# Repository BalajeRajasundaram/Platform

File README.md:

# Platform
SAMD20 Base board

Using https://github.com/SchrodingersGat/KiBoM for BOM generation.

Using https://github.com/ian-ross/kicad-plugins for auto placement of components initially.

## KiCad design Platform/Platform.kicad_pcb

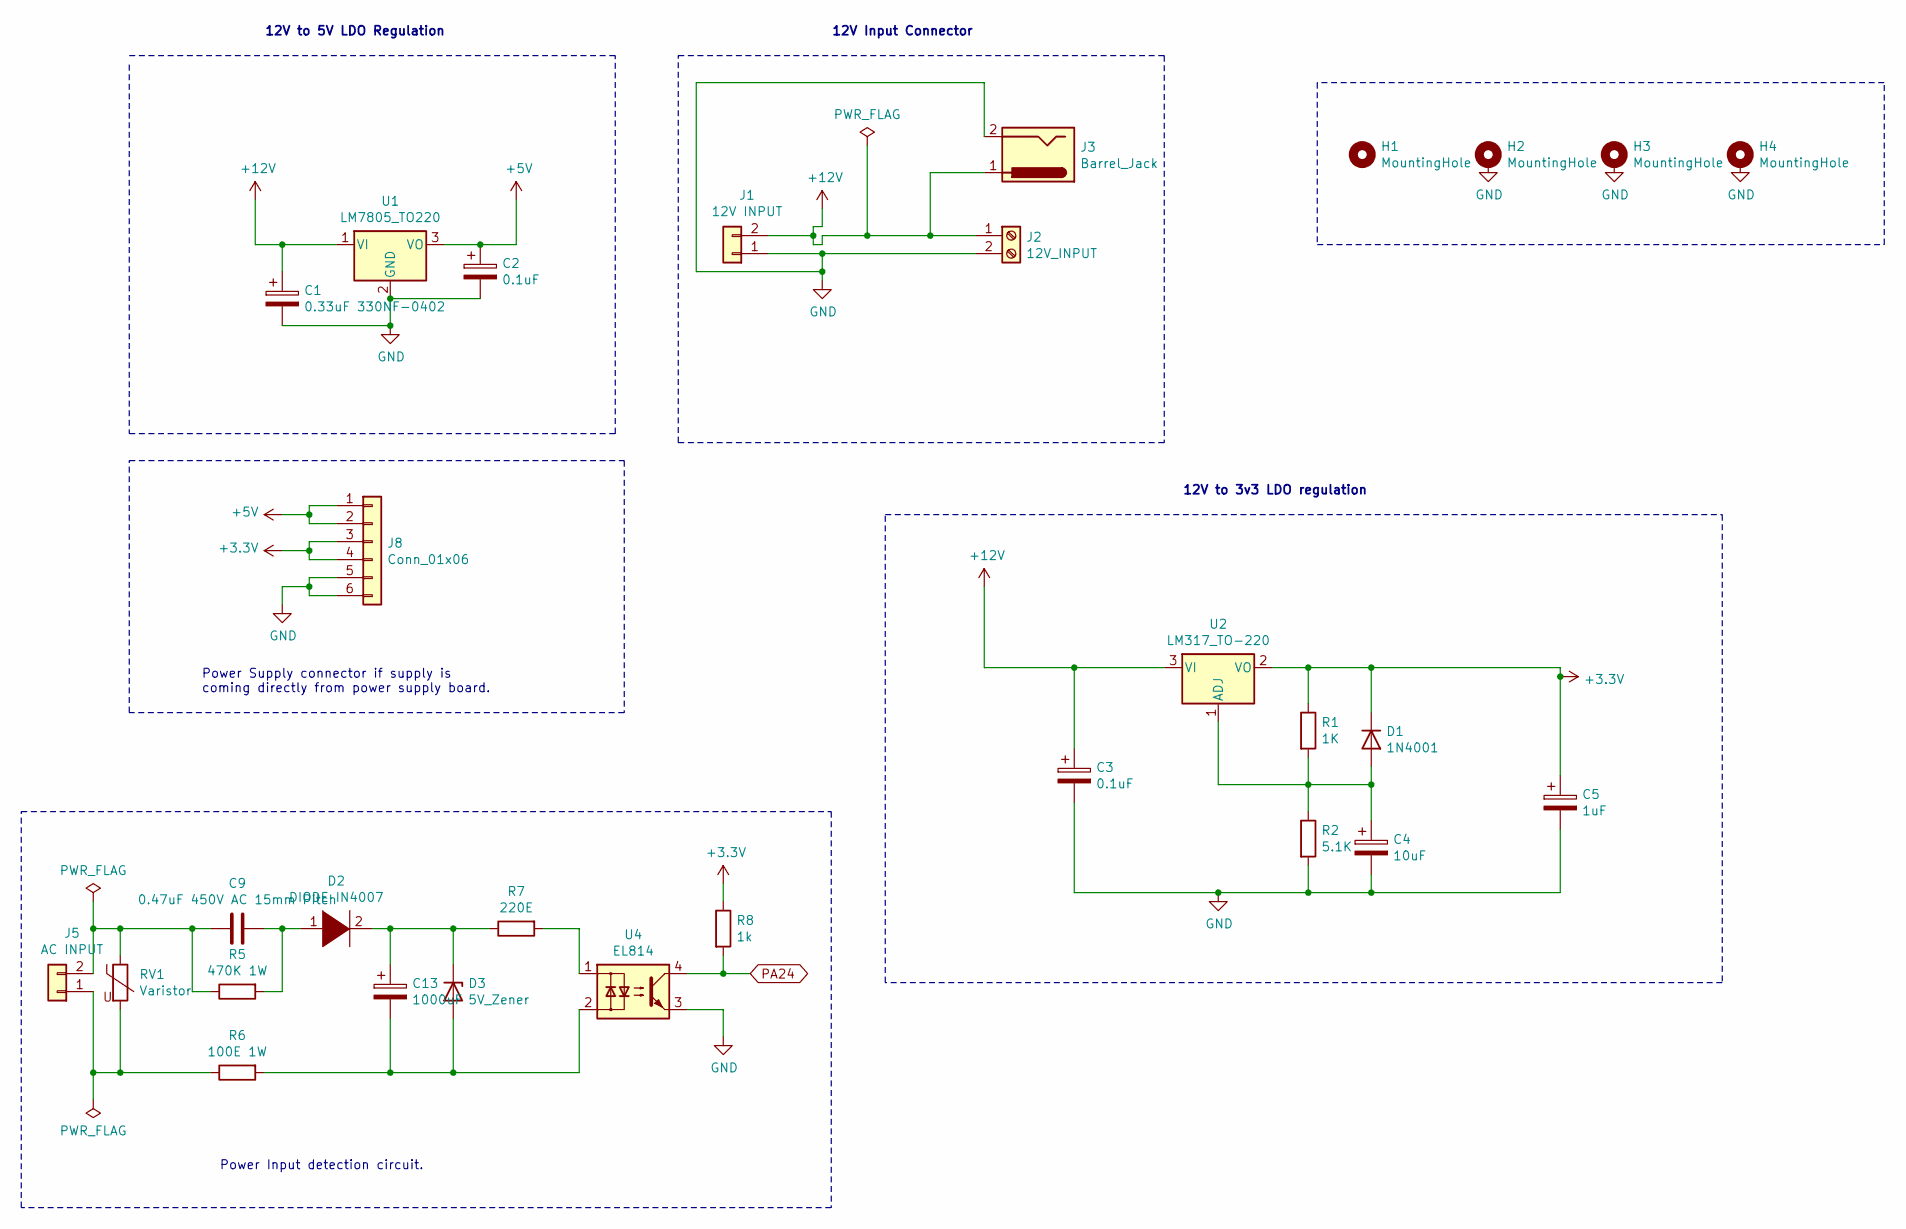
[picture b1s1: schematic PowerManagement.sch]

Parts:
C1: 0.33uF 330NF-0402; C_0402_1005Metric
C2, C3: 0.1uF; C_0402_1005Metric
C4: 10uF; CP_Radial_Tantal_D5.0mm_P5.00mm
C5: 1uF; CP_Radial_Tantal_D5.0mm_P5.00mm
C9: 0.47uF 450V AC 15mm Pitch; C_Rect_L7.2mm_W5.5mm_P5.00mm_FKS2_FKP2_MKS2_MKP2
C13: 1000uF; CP_Radial_D10.0mm_P2.50mm
D1: 1N4001; D_DO-41_SOD81_P10.16mm_Horizontal
D2: DIODE IN4007; D_DO-41_SOD81_P10.16mm_Horizontal
D3: 5V_Zener; D_DO-35_SOD27_P7.62mm_Horizontal
H1, H2, H3, H4: MountingHole; MountingHole_3.2mm_M3_DIN965_Pad
J1: 12V INPUT; TerminalBlock_Phoenix_MKDS-1,5-2_1x02_P5.00mm_Horizontal
J2: 12V_INPUT; PinHeader_1x02_P2.54mm_Vertical
J3: Barrel_Jack; BarrelJack_Horizontal
J5: AC INPUT; TerminalBlock_Phoenix_MKDS-1,5-2_1x02_P5.00mm_Horizontal
J8: Conn_01x06; Molex_KK-254_AE-6410-06A_1x06_P2.54mm_Vertical
R1: 1K; R_0603_1608Metric
R2: 5.1K; R_0603_1608Metric
R5: 470K 1W; R_Axial_DIN0411_L9.9mm_D3.6mm_P12.70mm_Horizontal
R6: 100E 1W; R_Axial_DIN0411_L9.9mm_D3.6mm_P12.70mm_Horizontal
R7: 220E; R_0603_1608Metric
R8: 1k; R_0603_1608Metric
RV1: Varistor; RV_Disc_D7mm_W3.4mm_P5mm
U1: LM7805_TO220; TO-220-3_Vertical
U2: LM317_TO-220; TO-220-3_Vertical
U4: EL814; Luna_NSL-32

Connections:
+3V3: C5.1, D1.1 (K), J8.3, J8.4, R1.1, R8.1, U2.2 (VO); also elsewhere on the board
+5V: C2.1, J8.1, J8.2, U1.3 (VO); also elsewhere on the board
+12V: C1.1, C3.1, J1.2, J2.1, J3.1, U1.1 (VI), U2.3 (VI)
GND: C1.2, C2.2, C3.2, C4.2, C5.2, J1.1, J2.2, J3.2, J8.5, J8.6, R2.2, U1.2 (GND), U4.3; also elsewhere on the board
unnamed: C4.1, D1.2 (A), R1.2, R2.1, U2.1 (ADJ)
unnamed: C9.1, J5.2, R5.1, RV1.1
unnamed: C9.2, D2.1 (K), R5.2
unnamed: C13.1, D2.2 (A), D3.1 (K), R7.1
unnamed: C13.2, D3.2 (A), R6.2, U4.2
unnamed: J5.1, R6.1, RV1.2
unnamed: R7.2, U4.1
PA24: R8.2, U4.4; also elsewhere on the board

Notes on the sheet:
12V Input Connector
12V to 5V LDO Regulation
12V to 3v3 LDO regulation
Power Supply connector if supply is coming directly from power supply board.
Power Input detection circuit.

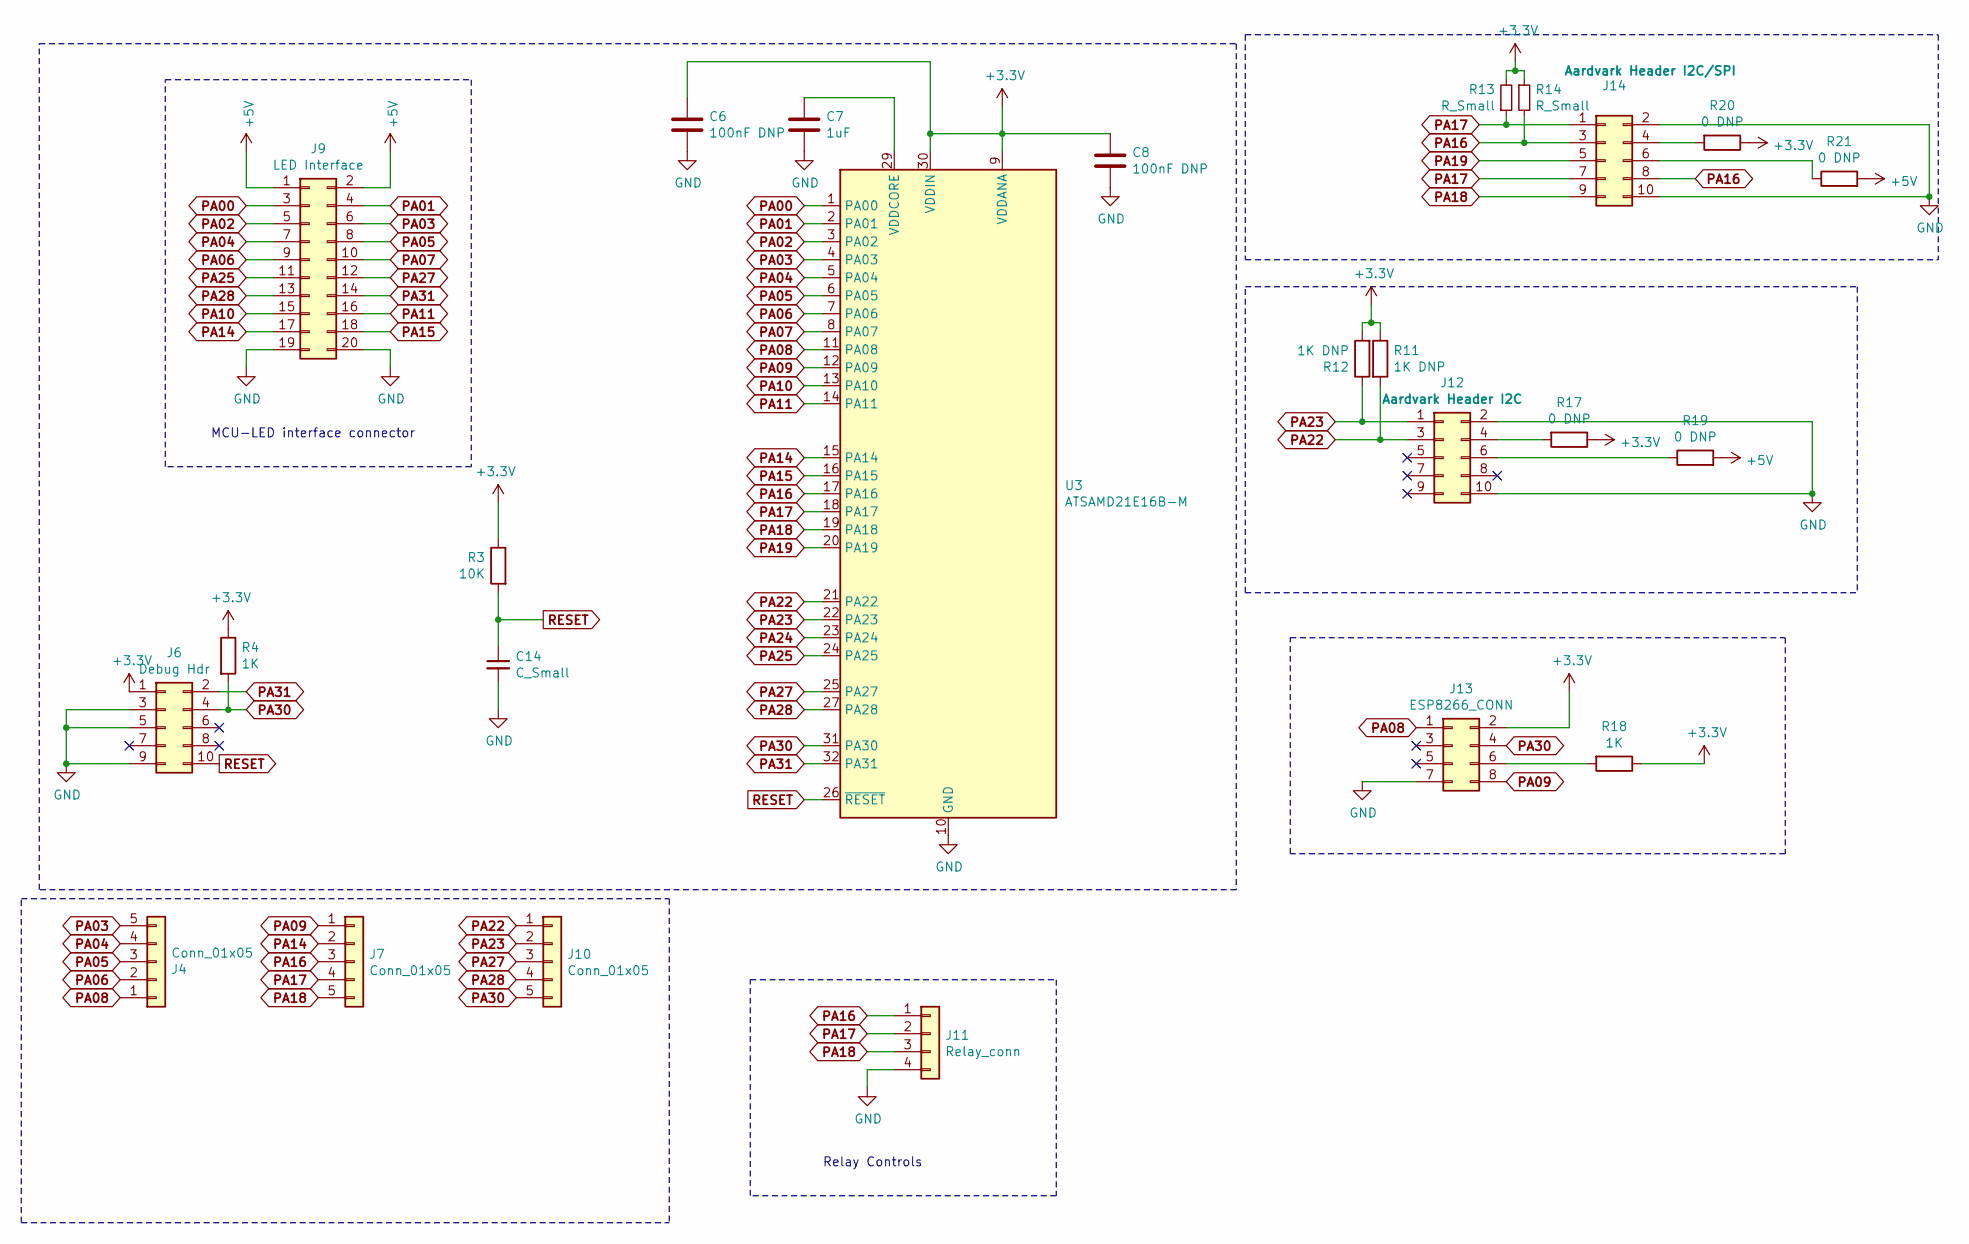
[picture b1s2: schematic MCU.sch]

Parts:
C6, C8: 100nF DNP; C_0402_1005Metric
C7: 1uF; C_0402_1005Metric
C14: C_Small; C_0402_1005Metric
J4, J7, J10: Conn_01x05; PinHeader_1x05_P2.54mm_Vertical
J6: Debug Hdr; PinHeader_2x05_P2.54mm_Vertical
J9: LED Interface; PinHeader_2x10_P2.54mm_Horizontal
J11: Relay_conn; Molex_KK-254_AE-6410-04A_1x04_P2.54mm_Vertical
J12: Aardvark Header I2C; PinHeader_2x05_P2.54mm_Vertical
J13: ESP8266_CONN; PinHeader_2x04_P2.54mm_Vertical
J14: Aardvark Header I2C/SPI; PinHeader_2x05_P2.54mm_Vertical
R3: 10K; R_0603_1608Metric
R4, R18: 1K; R_0603_1608Metric
R11, R12: 1K DNP; R_0603_1608Metric
R13, R14: R_Small; R_0603_1608Metric
R17, R19, R20, R21: 0 DNP; R_0603_1608Metric
U3: ATSAMD21E16B-M; QFN-32-1EP_5x5mm_P0.5mm_EP3.6x3.6mm

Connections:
+3V3: C6.1, C8.1, J6.1, J13.2, R3.1, R4.1, R11.1, R12.2, R13.2, R14.1, R17.1, R18.1, R20.1, U3.9 (VDDANA), U3.30 (VDDIN); also elsewhere on the board
+5V: J9.1, J9.2, R19.2, R21.2; also elsewhere on the board
GND: C6.2, C7.2, C8.2, C14.2, J6.3, J6.5, J6.9, J9.19, J9.20, J11.4, J12.2, J12.10, J13.7, J14.2, J14.10, U3.10 (GND), U3.28 (GND); also elsewhere on the board
unnamed: C7.1, U3.29 (VDDCORE)
unnamed: J12.4, R17.2
unnamed: J12.6, R19.1
unnamed: J13.6, R18.2
unnamed: J14.4, R20.2
unnamed: J14.6, R21.1
PA00: J9.3, U3.1 (PA00)
PA01: J9.4, U3.2 (PA01)
PA02: J9.5, U3.3 (PA02)
PA03: J4.5, J9.6, U3.4 (PA03)
PA04: J4.4, J9.7, U3.5 (PA04)
PA05: J4.3, J9.8, U3.6 (PA05)
PA06: J4.2, J9.9, U3.7 (PA06)
PA07: J9.10, U3.8 (PA07)
PA08: J4.1, J13.1, U3.11 (PA08)
PA09: J7.1, J13.8, U3.12 (PA09)
PA10: J9.15, U3.13 (PA10)
PA11: J9.16, U3.14 (PA11)
PA14: J7.2, J9.17, U3.15 (PA14)
PA15: J9.18, U3.16 (PA15)
PA16: J7.3, J11.1, J14.3, J14.8, R14.2, U3.17 (PA16)
PA17: J7.4, J11.2, J14.1, J14.7, R13.1, U3.18 (PA17)
PA18: J7.5, J11.3, J14.9, U3.19 (PA18)
PA19: J14.5, U3.20 (PA19)
PA22: J10.1, J12.3, R11.2, U3.21 (PA22); also elsewhere on the board
PA23: J10.2, J12.1, R12.1, U3.22 (PA23); also elsewhere on the board
PA24: U3.23 (PA24); also elsewhere on the board
PA25: J9.11, U3.24 (PA25)
PA27: J9.12, J10.3, U3.25 (PA27)
PA28: J9.13, J10.4, U3.27 (PA28)
PA30: J6.4, J10.5, J13.4, R4.2, U3.31 (PA30)
PA31: J6.2, J9.14, U3.32 (PA31)
RESET: C14.1, J6.10, R3.2, U3.26 (~RESET)

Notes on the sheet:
MCU-LED interface connector
Relay Controls

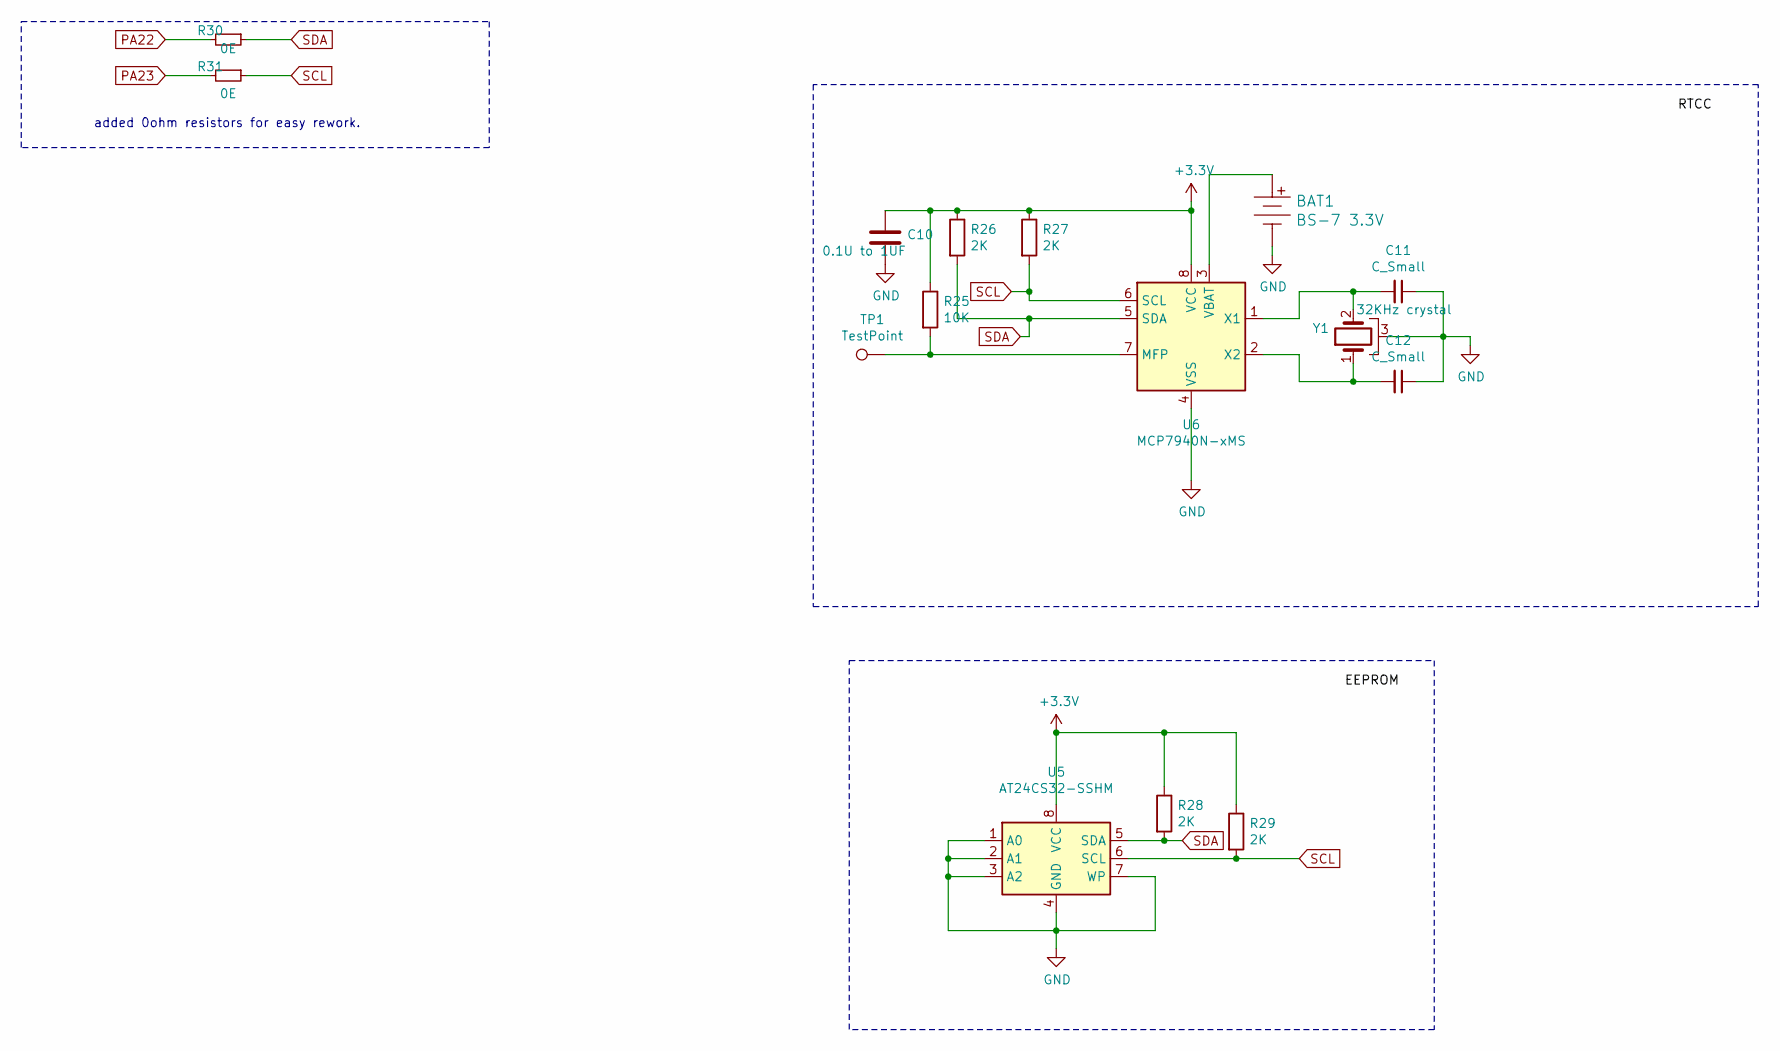
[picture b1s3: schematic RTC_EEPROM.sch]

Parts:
BAT1: BS-7 3.3V; BatteryHolder_Keystone_103_1x20mm; MPN BS-7; Digi-Key_PN BS-7-ND
C10: 0.1U to 1UF; C_0402_1005Metric
C11, C12: C_Small; C_0402_1005Metric
R25: 10K; R_0603_1608Metric
R26, R27, R28, R29: 2K; R_0603_1608Metric
R30, R31: 0E; R_0603_1608Metric
TP1: TestPoint; TestPoint_Pad_D2.5mm
U5: AT24CS32-SSHM; SOIC-8_3.9x4.9mm_P1.27mm
U6: MCP7940N-xMS; SOIC-8_3.9x4.9mm_P1.27mm
Y1: 32KHz crystal; Crystal_AT310_D3.0mm_L10.0mm_Horizontal_1EP_style2

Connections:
+3V3: C10.1, R25.1, R26.1, R27.1, R28.1, R29.1, U5.8 (VCC), U6.8 (VCC); also elsewhere on the board
GND: BAT1.Neg, C10.2, C11.1, C12.1, U5.1 (A0), U5.2 (A1), U5.3 (A2), U5.4 (GND), U5.7 (WP), U6.4 (VSS), Y1.3; also elsewhere on the board
unnamed: BAT1.Pos, U6.3 (VBAT)
unnamed: C11.2, U6.1 (X1), Y1.2
unnamed: C12.2, U6.2 (X2), Y1.1
unnamed: R25.2, TP1.1, U6.7 (MFP)
PA22: R30.2; also elsewhere on the board
PA23: R31.2; also elsewhere on the board
SCL: R27.2, R29.2, R31.1, U5.6 (SCL), U6.6 (SCL)
SDA: R26.2, R28.2, R30.1, U5.5 (SDA), U6.5 (SDA)

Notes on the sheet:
added 0ohm resistors for easy rework.

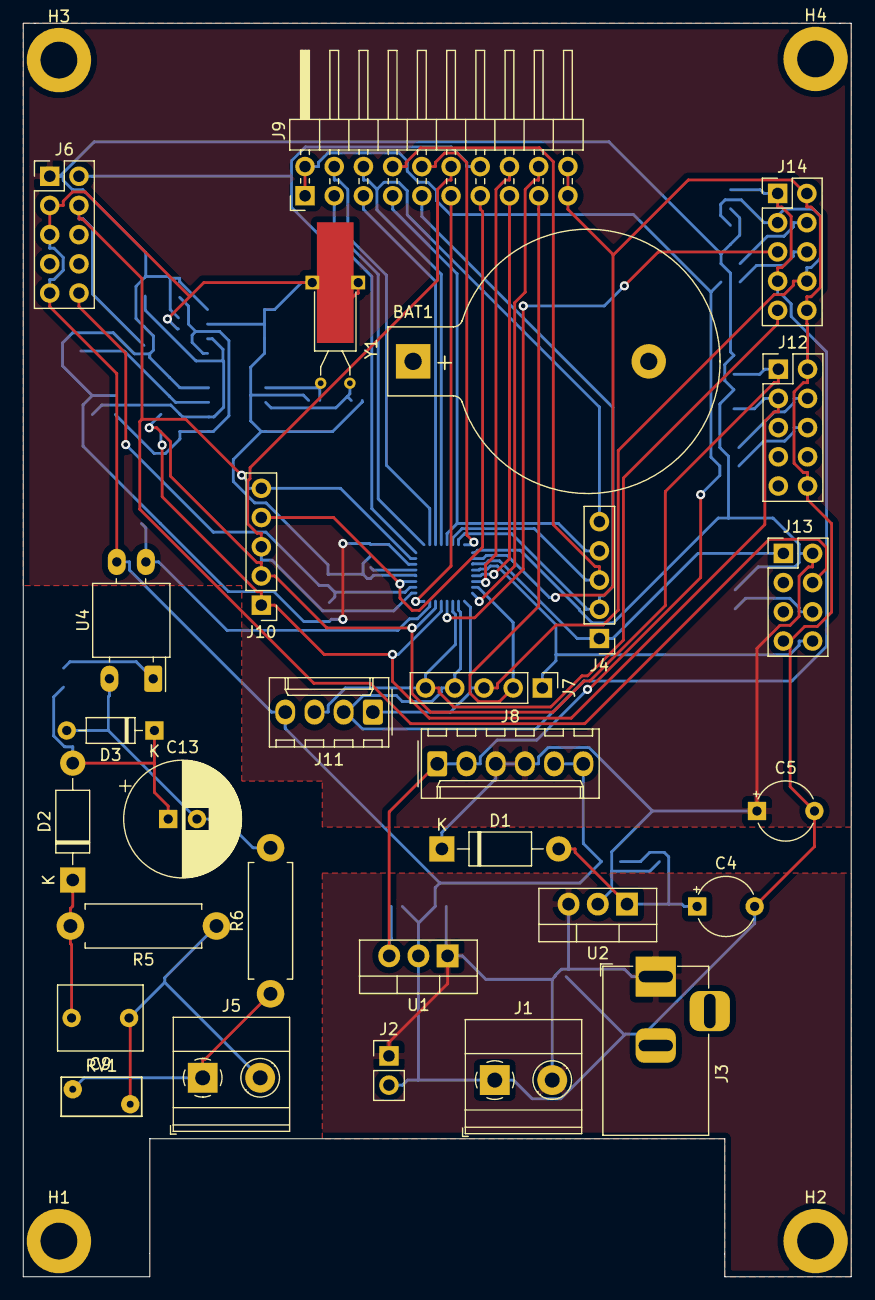
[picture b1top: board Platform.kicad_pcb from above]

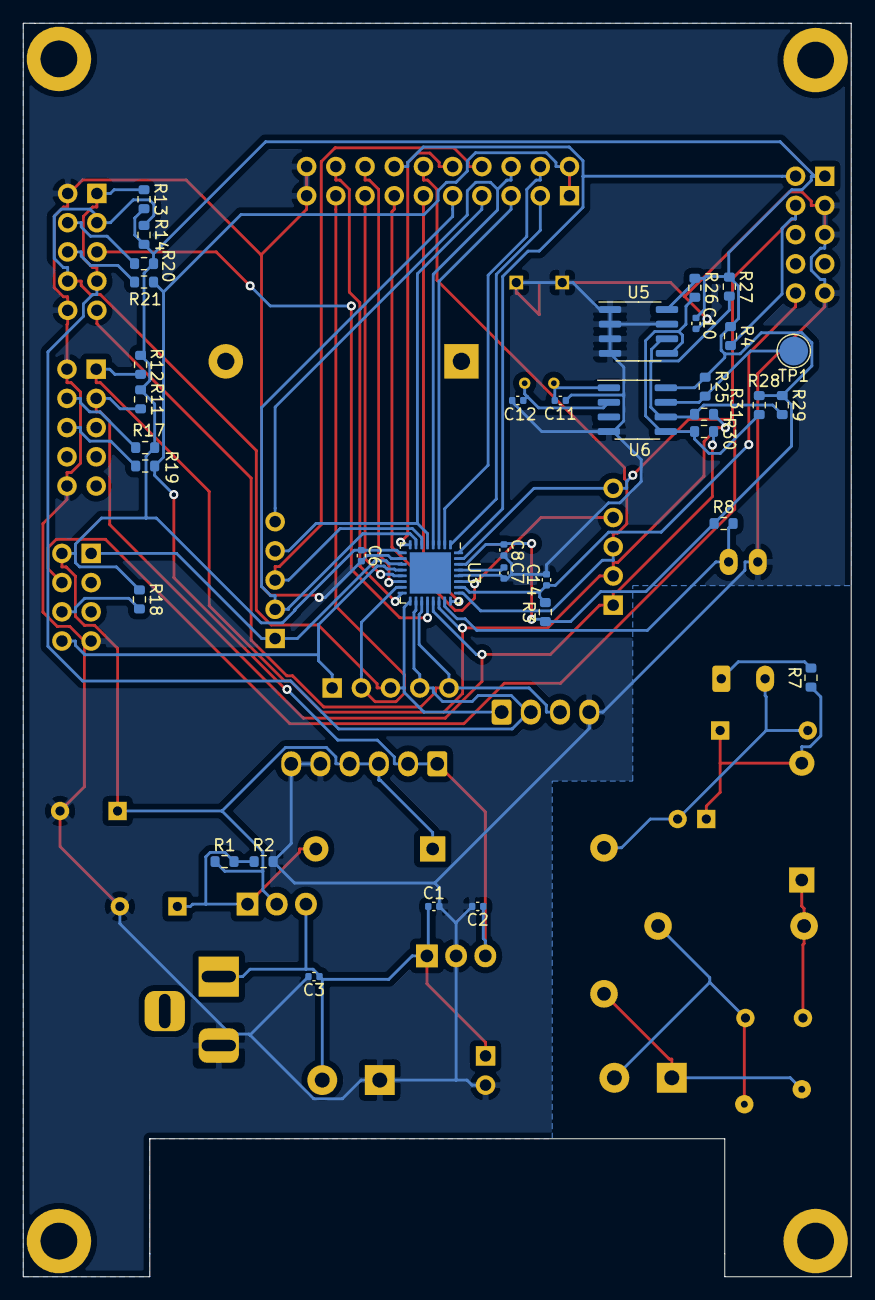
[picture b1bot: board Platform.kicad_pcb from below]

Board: 2 copper layers, 72.0 x 109.0 mm, 69 parts (36 on the bottom side), 49 nets.

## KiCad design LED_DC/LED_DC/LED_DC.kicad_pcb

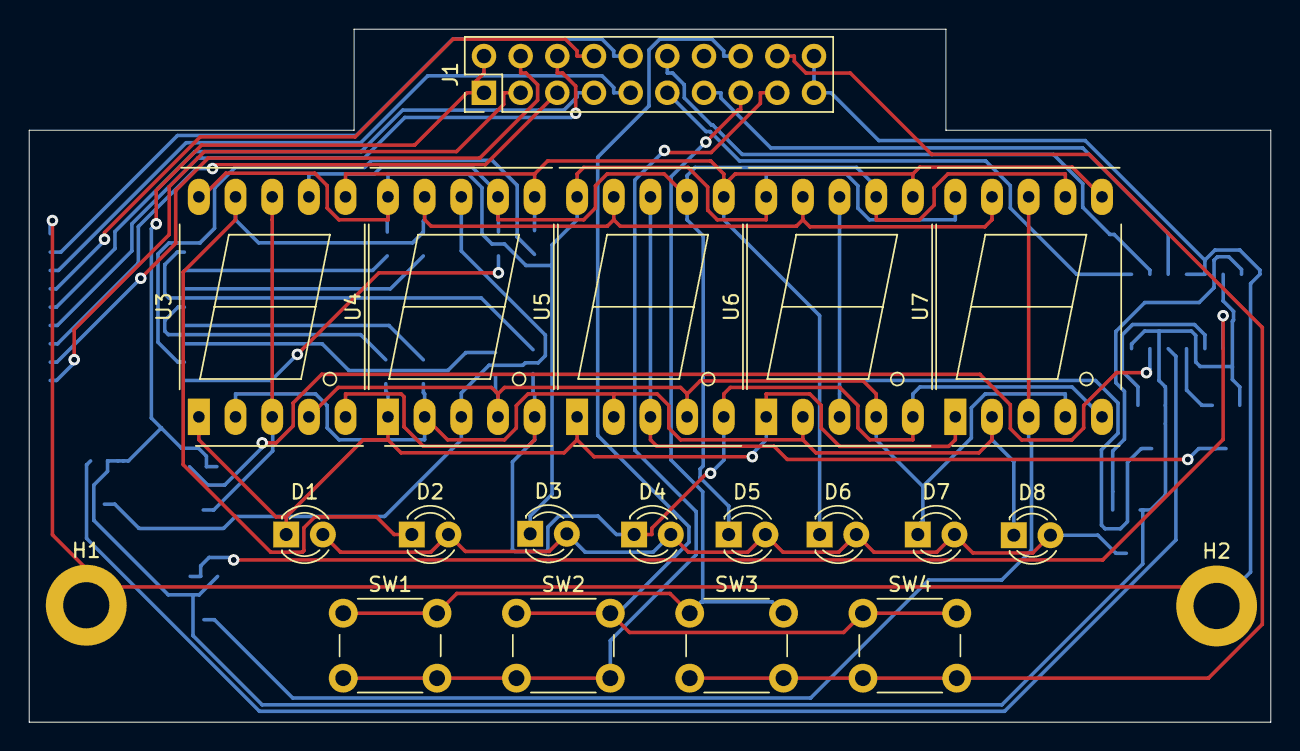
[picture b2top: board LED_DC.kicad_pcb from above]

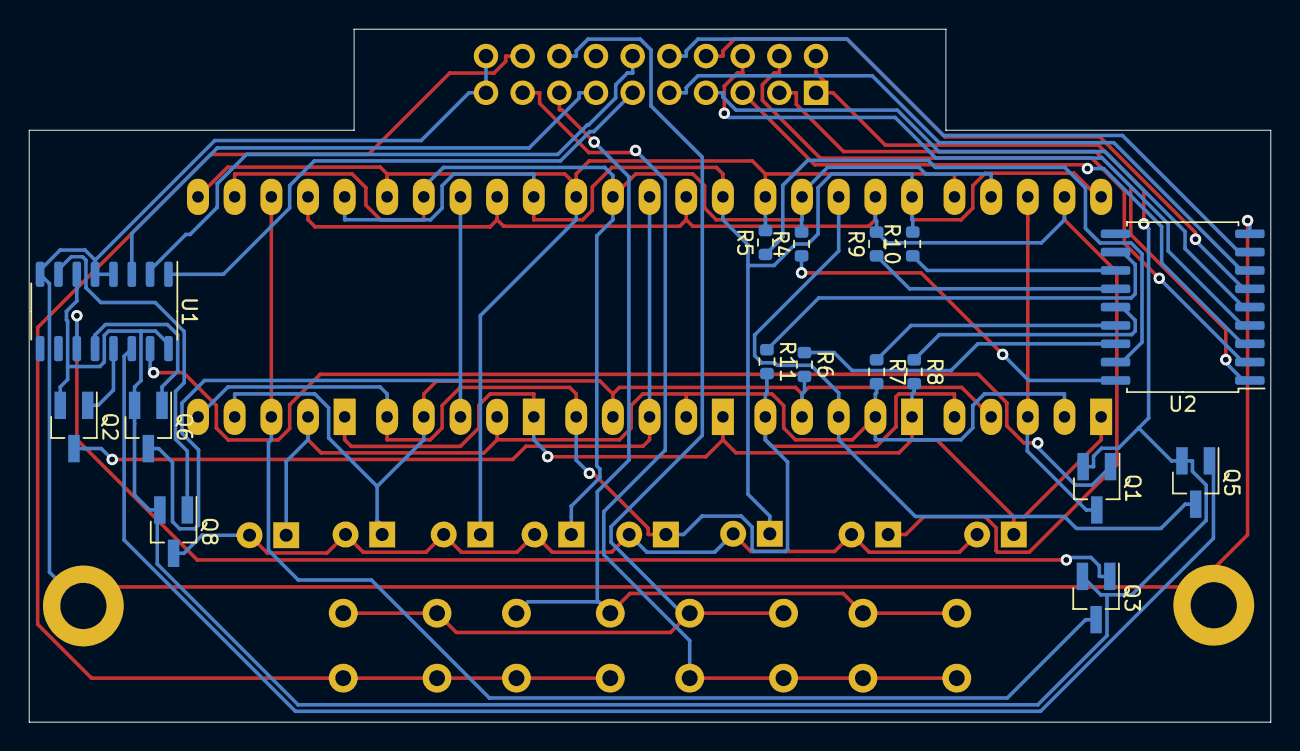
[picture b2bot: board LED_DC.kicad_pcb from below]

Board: 2 copper layers, 86.0 x 48.0 mm, 36 parts (16 on the bottom side), 45 nets.

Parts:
D1, D2, D3, D4, D5, D6, D7, D8: LED; LED_D3.0mm
H1, H2: MountingHole_Pad; MountingHole_3.2mm_M3_DIN965_Pad
J1: MCU interface; PinHeader_2x10_P2.54mm_Vertical
Q1, Q2, Q3, Q5, Q6, Q8: FDV304P; SOT-23_Handsoldering
R4, R5, R6, R7, R8, R9, R10, R11: R; R_0603_1608Metric
SW1, SW2, SW3, SW4: SW_Push_45deg; SW_PUSH_6mm
U1: 74HC238; SO-16_3.9x9.9mm_P1.27mm
U2: ULN2803A; SOIC-18W_7.5x11.6mm_P1.27mm
U3, U4, U5, U6, U7: KCSA02-136; 7SegmentLED_LTS6760_LTS6780

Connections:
+5V: J1.1, J1.2, Q1.2, Q2.2, Q3.2, Q5.2, Q6.2, Q8.2, U1.6, U1.16
A: D5.1, R4.2, U3.7, U4.7, U5.7, U6.7, U7.7
B: D6.1, R5.2, U3.6, U4.6, U5.6, U6.6, U7.6
C: D7.1, R6.2, U3.4, U4.4, U5.4, U6.4, U7.4
C1: J1.11, U1.1
C2: J1.12, U1.2
C3: J1.13, U1.3
D: D8.1, R7.2, U3.2, U4.2, U5.2, U6.2, U7.2
D0: J1.3, U2.1
D1: J1.4, U2.2
D2: J1.5, U2.3
D3: J1.6, U2.4
D4: J1.7, U2.5
D5: J1.8, U2.6
D6: J1.9, U2.7
D7: J1.10, U2.8
DP: D4.1, R11.2, U3.5, U4.5, U5.5, U6.5, U7.5
D_1: Q1.3, U3.3, U3.8
D_2: Q5.3, U4.3, U4.8
D_3: Q2.3, U5.3, U5.8
D_4: Q6.3, U6.3, U6.8
D_5: Q3.3, U7.3, U7.8
D_8: D1.2, D2.2, D3.2, D4.2, D5.2, D6.2, D7.2, D8.2, Q8.3
D_C_1: Q1.1, U1.15
D_C_2: Q5.1, U1.14
D_C_3: Q2.1, U1.13
D_C_4: Q6.1, U1.12
D_C_5: Q3.1, U1.11
D_C_8: Q8.1, U1.7
E: D1.1, R8.2, U3.1, U4.1, U5.1, U6.1, U7.1
F: D2.1, R9.2, U3.9, U4.9, U5.9, U6.9, U7.9
G: D3.1, R10.2, U3.10, U4.10, U5.10, U6.10, U7.10
GND: H1.1, H2.1, J1.19, J1.20, U1.4, U1.5, U1.8, U2.9
KEY_COL1: J1.17, SW1.2, SW2.2
KEY_COL2: J1.18, SW3.2, SW4.2
KEY_ROW1: J1.15, SW1.1, SW3.1
KEY_ROW2: J1.16, SW2.1, SW4.1
unnamed: R4.1, U2.18
unnamed: R5.1, U2.17
unnamed: R6.1, U2.16
unnamed: R7.1, U2.15
unnamed: R8.1, U2.14
unnamed: R9.1, U2.13
unnamed: R10.1, U2.12
unnamed: R11.1, U2.11

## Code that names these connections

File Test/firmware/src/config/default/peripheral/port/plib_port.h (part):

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// *****************************************************************************
// *****************************************************************************

/*** Macros for GPIO_PA00 pin ***/
#define GPIO_PA00_Set()               (PORT_REGS->GROUP[0].PORT_OUTSET = ((uint32_t)1U << 0U))
#define GPIO_PA00_Clear()             (PORT_REGS->GROUP[0].PORT_OUTCLR = ((uint32_t)1U << 0U))
#define GPIO_PA00_Toggle()            (PORT_REGS->GROUP[0].PORT_OUTTGL = ((uint32_t)1U << 0U))
#define GPIO_PA00_OutputEnable()      (PORT_REGS->GROUP[0].PORT_DIRSET = ((uint32_t)1U << 0U))
#define GPIO_PA00_InputEnable()       (PORT_REGS->GROUP[0].PORT_DIRCLR = ((uint32_t)1U << 0U))
#define GPIO_PA00_Get()               (((PORT_REGS->GROUP[0].PORT_IN >> 0U)) & 0x01U)
#define GPIO_PA00_PIN                  PORT_PIN_PA00

/*** Macros for GPIO_PA01 pin ***/
#define GPIO_PA01_Set()               (PORT_REGS->GROUP[0].PORT_OUTSET = ((uint32_t)1U << 1U))
#define GPIO_PA01_Clear()             (PORT_REGS->GROUP[0].PORT_OUTCLR = ((uint32_t)1U << 1U))
#define GPIO_PA01_Toggle()            (PORT_REGS->GROUP[0].PORT_OUTTGL = ((uint32_t)1U << 1U))
#define GPIO_PA01_OutputEnable()      (PORT_REGS->GROUP[0].PORT_DIRSET = ((uint32_t)1U << 1U))
#define GPIO_PA01_InputEnable()       (PORT_REGS->GROUP[0].PORT_DIRCLR = ((uint32_t)1U << 1U))
#define GPIO_PA01_Get()               (((PORT_REGS->GROUP[0].PORT_IN >> 1U)) & 0x01U)
#define GPIO_PA01_PIN                  PORT_PIN_PA01

/*** Macros for GPIO_PA02 pin ***/
#define GPIO_PA02_Set()               (PORT_REGS->GROUP[0].PORT_OUTSET = ((uint32_t)1U << 2U))
#define GPIO_PA02_Clear()             (PORT_REGS->GROUP[0].PORT_OUTCLR = ((uint32_t)1U << 2U))
#define GPIO_PA02_Toggle()            (PORT_REGS->GROUP[0].PORT_OUTTGL = ((uint32_t)1U << 2U))
#define GPIO_PA02_OutputEnable()      (PORT_REGS->GROUP[0].PORT_DIRSET = ((uint32_t)1U << 2U))
#define GPIO_PA02_InputEnable()       (PORT_REGS->GROUP[0].PORT_DIRCLR = ((uint32_t)1U << 2U))
#define GPIO_PA02_Get()               (((PORT_REGS->GROUP[0].PORT_IN >> 2U)) & 0x01U)
#define GPIO_PA02_PIN                  PORT_PIN_PA02

/*** Macros for GPIO_PA03 pin ***/
#define GPIO_PA03_Set()               (PORT_REGS->GROUP[0].PORT_OUTSET = ((uint32_t)1U << 3U))
#define GPIO_PA03_Clear()             (PORT_REGS->GROUP[0].PORT_OUTCLR = ((uint32_t)1U << 3U))
#define GPIO_PA03_Toggle()            (PORT_REGS->GROUP[0].PORT_OUTTGL = ((uint32_t)1U << 3U))
#define GPIO_PA03_OutputEnable()      (PORT_REGS->GROUP[0].PORT_DIRSET = ((uint32_t)1U << 3U))
#define GPIO_PA03_InputEnable()       (PORT_REGS->GROUP[0].PORT_DIRCLR = ((uint32_t)1U << 3U))
#define GPIO_PA03_Get()               (((PORT_REGS->GROUP[0].PORT_IN >> 3U)) & 0x01U)
#define GPIO_PA03_PIN                  PORT_PIN_PA03

/*** Macros for GPIO_PA04 pin ***/
#define GPIO_PA04_Set()               (PORT_REGS->GROUP[0].PORT_OUTSET = ((uint32_t)1U << 4U))
#define GPIO_PA04_Clear()             (PORT_REGS->GROUP[0].PORT_OUTCLR = ((uint32_t)1U << 4U))
#define GPIO_PA04_Toggle()            (PORT_REGS->GROUP[0].PORT_OUTTGL = ((uint32_t)1U << 4U))
#define GPIO_PA04_OutputEnable()      (PORT_REGS->GROUP[0].PORT_DIRSET = ((uint32_t)1U << 4U))
#define GPIO_PA04_InputEnable()       (PORT_REGS->GROUP[0].PORT_DIRCLR = ((uint32_t)1U << 4U))
#define GPIO_PA04_Get()               (((PORT_REGS->GROUP[0].PORT_IN >> 4U)) & 0x01U)
#define GPIO_PA04_PIN                  PORT_PIN_PA04

/*** Macros for GPIO_PA05 pin ***/
#define GPIO_PA05_Set()               (PORT_REGS->GROUP[0].PORT_OUTSET = ((uint32_t)1U << 5U))
#define GPIO_PA05_Clear()             (PORT_REGS->GROUP[0].PORT_OUTCLR = ((uint32_t)1U << 5U))
#define GPIO_PA05_Toggle()            (PORT_REGS->GROUP[0].PORT_OUTTGL = ((uint32_t)1U << 5U))
#define GPIO_PA05_OutputEnable()      (PORT_REGS->GROUP[0].PORT_DIRSET = ((uint32_t)1U << 5U))
#define GPIO_PA05_InputEnable()       (PORT_REGS->GROUP[0].PORT_DIRCLR = ((uint32_t)1U << 5U))
#define GPIO_PA05_Get()               (((PORT_REGS->GROUP[0].PORT_IN >> 5U)) & 0x01U)
#define GPIO_PA05_PIN                  PORT_PIN_PA05

/*** Macros for GPIO_PA06 pin ***/
#define GPIO_PA06_Set()               (PORT_REGS->GROUP[0].PORT_OUTSET = ((uint32_t)1U << 6U))
#define GPIO_PA06_Clear()             (PORT_REGS->GROUP[0].PORT_OUTCLR = ((uint32_t)1U << 6U))
#define GPIO_PA06_Toggle()            (PORT_REGS->GROUP[0].PORT_OUTTGL = ((uint32_t)1U << 6U))
#define GPIO_PA06_OutputEnable()      (PORT_REGS->GROUP[0].PORT_DIRSET = ((uint32_t)1U << 6U))
#define GPIO_PA06_InputEnable()       (PORT_REGS->GROUP[0].PORT_DIRCLR = ((uint32_t)1U << 6U))
#define GPIO_PA06_Get()               (((PORT_REGS->GROUP[0].PORT_IN >> 6U)) & 0x01U)
#define GPIO_PA06_PIN                  PORT_PIN_PA06

/*** Macros for GPIO_PA07 pin ***/
#define GPIO_PA07_Set()               (PORT_REGS->GROUP[0].PORT_OUTSET = ((uint32_t)1U << 7U))
#define GPIO_PA07_Clear()             (PORT_REGS->GROUP[0].PORT_OUTCLR = ((uint32_t)1U << 7U))
#define GPIO_PA07_Toggle()            (PORT_REGS->GROUP[0].PORT_OUTTGL = ((uint32_t)1U << 7U))
#define GPIO_PA07_OutputEnable()      (PORT_REGS->GROUP[0].PORT_DIRSET = ((uint32_t)1U << 7U))
#define GPIO_PA07_InputEnable()       (PORT_REGS->GROUP[0].PORT_DIRCLR = ((uint32_t)1U << 7U))
#define GPIO_PA07_Get()               (((PORT_REGS->GROUP[0].PORT_IN >> 7U)) & 0x01U)
#define GPIO_PA07_PIN                  PORT_PIN_PA07

/*** Macros for GPIO_PA10 pin ***/
#define GPIO_PA10_Set()               (PORT_REGS->GROUP[0].PORT_OUTSET = ((uint32_t)1U << 10U))
#define GPIO_PA10_Clear()             (PORT_REGS->GROUP[0].PORT_OUTCLR = ((uint32_t)1U << 10U))
#define GPIO_PA10_Toggle()            (PORT_REGS->GROUP[0].PORT_OUTTGL = ((uint32_t)1U << 10U))
#define GPIO_PA10_OutputEnable()      (PORT_REGS->GROUP[0].PORT_DIRSET = ((uint32_t)1U << 10U))
#define GPIO_PA10_InputEnable()       (PORT_REGS->GROUP[0].PORT_DIRCLR = ((uint32_t)1U << 10U))
#define GPIO_PA10_Get()               (((PORT_REGS->GROUP[0].PORT_IN >> 10U)) & 0x01U)
#define GPIO_PA10_PIN                  PORT_PIN_PA10

/*** Macros for GPIO_PA11 pin ***/
#define GPIO_PA11_Set()               (PORT_REGS->GROUP[0].PORT_OUTSET = ((uint32_t)1U << 11U))
#define GPIO_PA11_Clear()             (PORT_REGS->GROUP[0].PORT_OUTCLR = ((uint32_t)1U << 11U))
#define GPIO_PA11_Toggle()            (PORT_REGS->GROUP[0].PORT_OUTTGL = ((uint32_t)1U << 11U))
#define GPIO_PA11_OutputEnable()      (PORT_REGS->GROUP[0].PORT_DIRSET = ((uint32_t)1U << 11U))
#define GPIO_PA11_InputEnable()       (PORT_REGS->GROUP[0].PORT_DIRCLR = ((uint32_t)1U << 11U))
#define GPIO_PA11_Get()               (((PORT_REGS->GROUP[0].PORT_IN >> 11U)) & 0x01U)
#define GPIO_PA11_PIN                  PORT_PIN_PA11

/*** Macros for GPIO_PA14 pin ***/
#define GPIO_PA14_Set()               (PORT_REGS->GROUP[0].PORT_OUTSET = ((uint32_t)1U << 14U))
#define GPIO_PA14_Clear()             (PORT_REGS->GROUP[0].PORT_OUTCLR = ((uint32_t)1U << 14U))
#define GPIO_PA14_Toggle()            (PORT_REGS->GROUP[0].PORT_OUTTGL = ((uint32_t)1U << 14U))
#define GPIO_PA14_OutputEnable()      (PORT_REGS->GROUP[0].PORT_DIRSET = ((uint32_t)1U << 14U))
#define GPIO_PA14_InputEnable()       (PORT_REGS->GROUP[0].PORT_DIRCLR = ((uint32_t)1U << 14U))
#define GPIO_PA14_Get()               (((PORT_REGS->GROUP[0].PORT_IN >> 14U)) & 0x01U)
#define GPIO_PA14_PIN                  PORT_PIN_PA14

/*** Macros for GPIO_PA15 pin ***/
#define GPIO_PA15_Set()               (PORT_REGS->GROUP[0].PORT_OUTSET = ((uint32_t)1U << 15U))
#define GPIO_PA15_Clear()             (PORT_REGS->GROUP[0].PORT_OUTCLR = ((uint32_t)1U << 15U))
#define GPIO_PA15_Toggle()            (PORT_REGS->GROUP[0].PORT_OUTTGL = ((uint32_t)1U << 15U))
#define GPIO_PA15_OutputEnable()      (PORT_REGS->GROUP[0].PORT_DIRSET = ((uint32_t)1U << 15U))
#define GPIO_PA15_InputEnable()       (PORT_REGS->GROUP[0].PORT_DIRCLR = ((uint32_t)1U << 15U))
#define GPIO_PA15_Get()               (((PORT_REGS->GROUP[0].PORT_IN >> 15U)) & 0x01U)
#define GPIO_PA15_PIN                  PORT_PIN_PA15

/*** Macros for GPIO_PA25 pin ***/
#define GPIO_PA25_Set()               (PORT_REGS->GROUP[0].PORT_OUTSET = ((uint32_t)1U << 25U))
#define GPIO_PA25_Clear()             (PORT_REGS->GROUP[0].PORT_OUTCLR = ((uint32_t)1U << 25U))
#define GPIO_PA25_Toggle()            (PORT_REGS->GROUP[0].PORT_OUTTGL = ((uint32_t)1U << 25U))
#define GPIO_PA25_OutputEnable()      (PORT_REGS->GROUP[0].PORT_DIRSET = ((uint32_t)1U << 25U))
#define GPIO_PA25_InputEnable()       (PORT_REGS->GROUP[0].PORT_DIRCLR = ((uint32_t)1U << 25U))
#define GPIO_PA25_Get()               (((PORT_REGS->GROUP[0].PORT_IN >> 25U)) & 0x01U)
#define GPIO_PA25_PIN                  PORT_PIN_PA25

/*** Macros for GPIO_PA27 pin ***/
#define GPIO_PA27_Set()               (PORT_REGS->GROUP[0].PORT_OUTSET = ((uint32_t)1U << 27U))
#define GPIO_PA27_Clear()             (PORT_REGS->GROUP[0].PORT_OUTCLR = ((uint32_t)1U << 27U))
#define GPIO_PA27_Toggle()            (PORT_REGS->GROUP[0].PORT_OUTTGL = ((uint32_t)1U << 27U))
#define GPIO_PA27_OutputEnable()      (PORT_REGS->GROUP[0].PORT_DIRSET = ((uint32_t)1U << 27U))
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
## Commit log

2020-11-15 Initial Version
2020-11-15 Added RTC and EEPROM
2020-11-21 Fixed ERC errors.
2020-11-22 added GPIO header for segment display.
2020-11-22 updated the crystal and cleared ERC errors.
2020-11-22 added caps for the crystal.
2020-11-22 Modified LED Drive using Direct GPIOs
2020-11-22 Removed redundant files
2020-11-29 Update README.md
    updated the info related to BOM generation.
2020-12-26 updated.
2020-12-27 updated the led schematic.
2020-12-27 Added keypad connector.
2021-01-03 Added foot prints for the components.
2021-01-05 updated the foot print assignment.
2021-01-17 updated the PCB.
2021-01-19 updated PCB.
2021-01-31 updated the schematic after feedback.
2021-01-31 updated the platform schematic.
2021-01-31 Added text to the schematic sections.
2021-02-01 updated platform schematic.
2021-02-02 Updated the schematic.
2021-02-04 Added Microcontroller pins xls.
2021-02-04 Updated the pins xls.
2021-02-07 added feedback for pin config excel sheet
2021-03-27 Updated Pin details# Please enter the commit message for your changes. Lines starting
2021-04-02 Updated IO xls to reflect all pins.
2021-04-02 updated the schematic as per the latest IO xls.
2021-04-03 Added power input detection circuit.
2021-04-03 added 20 pin header for LED interface.
2021-04-03 Added 20 pin header for MCU LED interface in LED schematic.
2021-04-04 Added connector for relay controls.
2021-04-04 GRM155R61C105KE01D
2021-04-06 updated Power detection
2021-04-08 Updated the PCB with component foot prints.
2021-04-19 updated the platform PCB.
2021-04-25 Updated the LED DC PCB.
2021-04-25 Updated LED DC.
2021-05-09 UPdated the PCB Gerber files.
2021-07-18 Updated component values.
2021-08-08 Added intial atmel start project.
2021-08-08 updated the atmel project to use 48MHz.
2021-08-08 added the atzip file.
2021-08-08 added the LED timer project.
2021-08-27 Added timer and flash modules to the project.
2021-08-27 Added segment.c files.
2021-09-12 Updated Firmware Project
2021-09-12 pseudo code for flash management added
2021-09-19 updated FSM
2021-09-26 overall schematics

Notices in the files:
Test/firmware/src/config/default/peripheral/port/plib_port.h:
Copyright (C) 2018 Microchip Technology Inc. and its subsidiaries.
